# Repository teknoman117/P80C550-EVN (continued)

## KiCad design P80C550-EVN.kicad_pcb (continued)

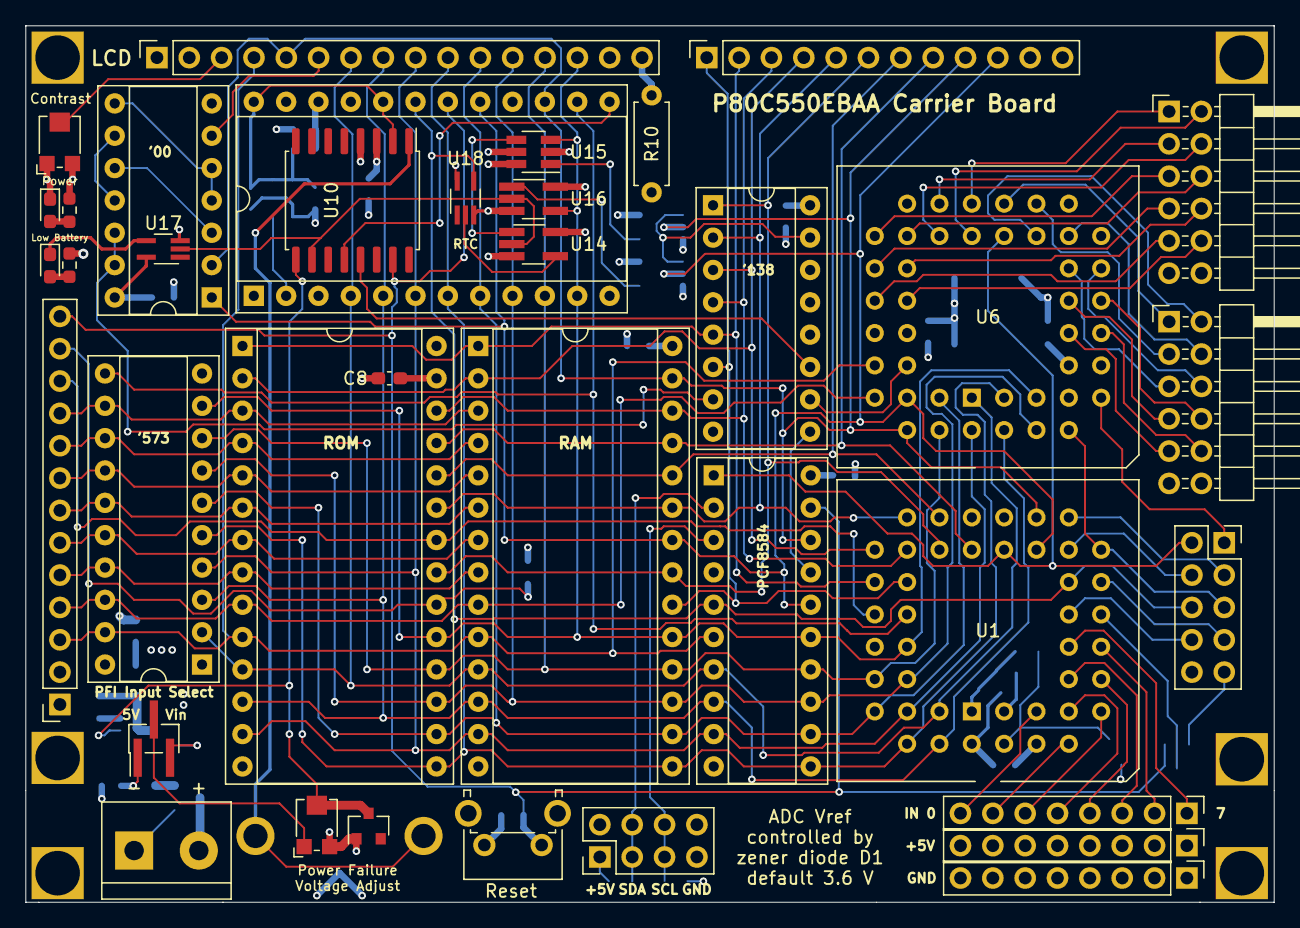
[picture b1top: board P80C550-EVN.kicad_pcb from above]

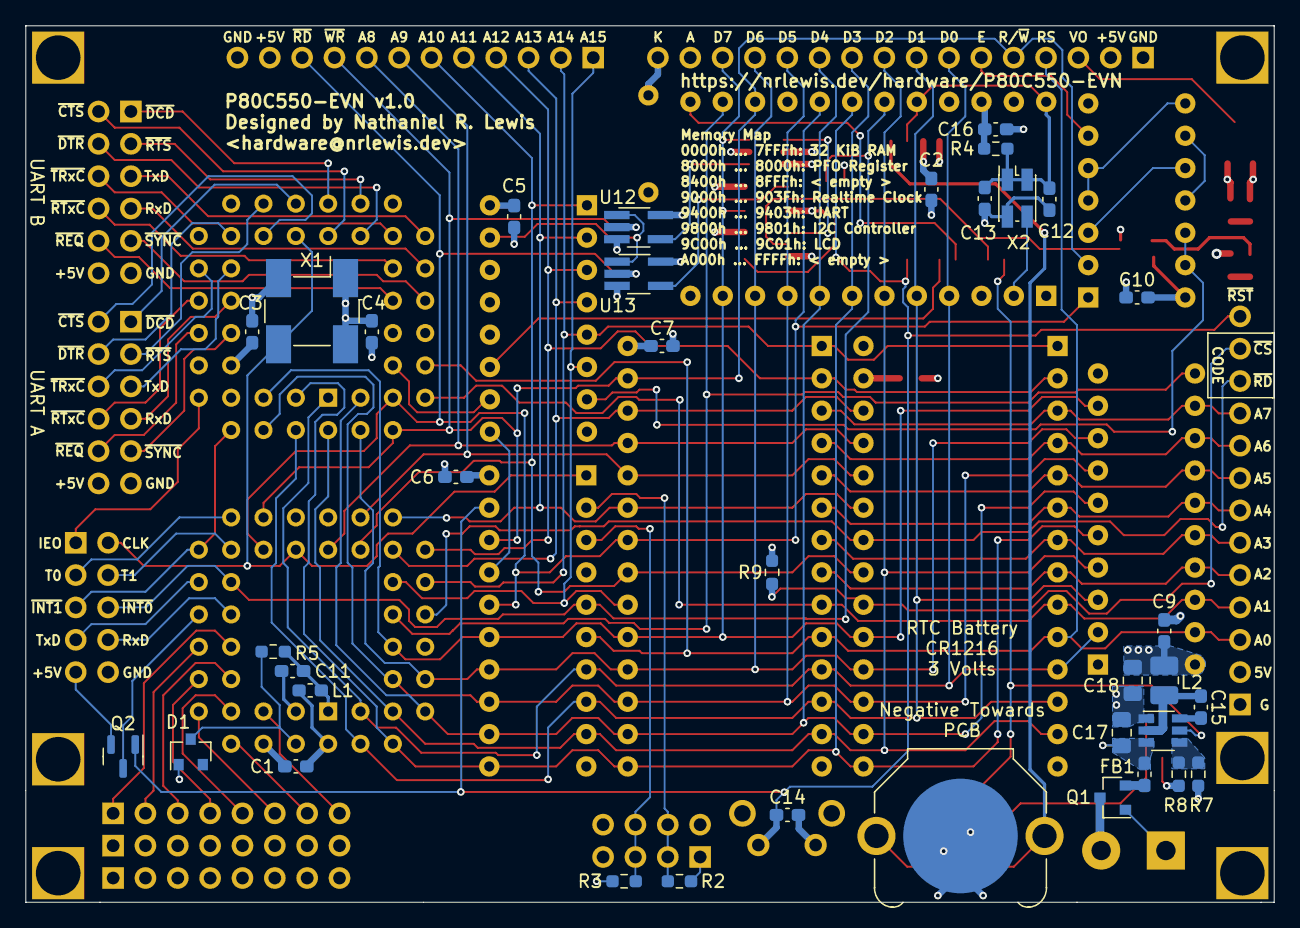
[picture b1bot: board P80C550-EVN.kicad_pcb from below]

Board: 4 copper layers, 98.0 x 68.8 mm, 79 parts (36 on the bottom side), 105 nets.

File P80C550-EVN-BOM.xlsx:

Component | Quantity | Quantity 5x | Part Name | Digikey Part Number | Digikey Website Link | Manufacturer Part Number
BT1 | 1 | 5 | RTC Backup | 36-3001-ND‎ | https://www.digikey.com/product-detail/en/3001/36-3001-ND/227442 | 3001
C16 | 1 | 5 | 5.1nF | 478-06033C512JAT4ACT-ND | https://www.digikey.com/en/products/detail/avx-corporation/0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 | 06033C512JAT4A
C17 | 1 | 5 | 10uF | 587-2985-1-ND | https://www.digikey.com/en/products/detail/taiyo-yuden/TMK21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 | TMK212BBJ106KG-T
C18 | 1 | 5 | 22uF | 587-5464-1-ND | https://www.digikey.com/en/products/detail/taiyo-yuden/LMK21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 | LMK212BBJ226MG-T
C1 C2 C3 C4 C5 C6 C7 C8 C9 C10 C11 C12 C13 C14 C15 | 15 | 75 | 0.1uF | 445-1316-1-ND‎ | https://www.digikey.com/product-detail/en/C1608X7R1E104K080A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 | C1608X7R1E104K080AA
D1 | 1 | 5 | 3.6V (zener) | 1727-5033-1-ND‎ | https://www.digikey.com/product-detail/en/BZX84-C3V6%2c215/1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 | BZX84-C3V6,215
D1 (alt) | 1 | 5 | 3.3V (zener) | 1727-2129-1-ND | https://www.digikey.com/en/products/detail/nexperia-usa-inc/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 | BZX84-C3V3,235
D2 | 1 | 5 | 5.1V (zener) | 1727-2130-1-ND‎ | https://www.digikey.com/product-detail/en/BZX84-C5V1%2c235/1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 | BZX84-C5V1,235
D3 | 1 | 5 | Blue | ‎1830-1068-1-ND‎ | https://www.digikey.com/product-detail/en/IN-S63BT5B/1830-10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 | IN-S63BT5B
D4 | 1 | 5 | Yellow | 1830-1072-1-ND‎ | https://www.digikey.com/product-detail/en/IN-S63BTR/1830-107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 | IN-S63BTR
FB1 | 1 | 5 | 100 @ 100 MHz | 587-1738-1-ND‎ | https://www.digikey.com/product-detail/en/FBMH1608HM101-T/58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 | FBMH1608HM101-T
J1 | 1 | 5 | VIN | 1920-1323-ND | https://www.digikey.com/en/products/detail/altech-corporatio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 | 34.102
J2 | 1 | 5 | Signals | S7108-ND | https://www.digikey.com/en/products/detail/PPPC052LFBN-RC/S7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 | PPPC052LFBN-RC
J3 | 1 | 5 | Address Low | S7046-ND | https://www.digikey.com/en/products/detail/PPPC131LFBN-RC/S7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 | PPPC131LFBN-RC
J4 | 1 | 5 | Address High | S7046-ND | https://www.digikey.com/en/products/detail/PPPC131LFBN-RC/S7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 | PPPC131LFBN-RC
J5 | 1 | 5 | LCD | S7049-ND | https://www.digikey.com/en/products/detail/PPPC161LFBN-RC/S7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 | PPPC161LFBN-RC
J6 J7 | 2 | 10 | UART | S2111EC-06-ND | https://www.digikey.com/en/products/detail/sullins-connector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 | PRPC006DBAN-M71RC
J8 | 1 | 5 | I2C | S2011EC-04-ND | https://www.digikey.com/en/products/detail/sullins-connector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 | PRPC004DAAN-RC
J9 J10 J11 | 3 | 15 | Analog In | S1011EC-08-ND | https://www.digikey.com/en/products/detail/sullins-connector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 | PRPC008SAAN-RC
JP1 | 1 | 5 | PFI Select | 952-3607-ND | https://www.digikey.com/en/products/detail/harwin-inc/M50-36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 | M50-3630342
L1 | 1 | 5 | 39uH | 712-1441-1-ND‎ | https://www.digikey.com/product-detail/en/L-14C39NJV4T/712-1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 | L-14C39NJV4T
L2 | 1 | 5 | 4.7uH | 535-12797-1-ND | https://www.digikey.com/en/products/detail/abracon-llc/AIML-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 | AIML-1008HC-4R7M-T
Q1 | 1 | 5 | Si2393DS | ‎742-SI2393DS-T1-GE3CT-ND‎ | https://www.digikey.com/product-detail/en/SI2393DS-T1-GE3/74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 | SI2393DS-T1-GE3
R1 R2 R3 R4 R5 R6 | 6 | 30 | 2K2 ohms | 118-CR0603-FX-2201ELFCT-ND‎ | https://www.digikey.com/product-detail/en/CR0603-FX-2201ELF/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 | CR0603-FX-2201ELF
R7 | 1 | 5 | 10K ohms | CR0603-FX-1002ELFCT-ND | https://www.digikey.com/en/products/detail/bourns-inc/CR0603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 | CR0603-FX-1002ELF
R8 | 1 | 5 | 52K3 ohms | CR0603-FX-5232ELFCT-ND | https://www.digikey.com/en/products/detail/bourns-inc/CR0603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 | CR0603-FX-5232ELF
R9 | 1 | 5 | 680 ohms | 118-CR0603-JW-681ELFCT-ND‎ | https://www.digikey.com/product-detail/en/CR0603-JW-681ELF/1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 | CR0603-JW-681ELF
R10 | 1 | 5 | 220 ohms
RV1 RV2 | 2 | 10 | 20K | TC33X-1-203ECT-ND | https://www.digikey.com/en/products/detail/TC33X-1-203E/TC33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 | TC33X-1-203E
SW1 | 1 | 5 | Reset | CKN10909-ND | https://www.digikey.com/en/products/detail/c-k/PTS645VM39-2-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 | PTS645VM39-2 LFS
U1 | 1 | 5 | P80C550EBAA
U10 | 1 | 5 | MAX691xWE
U11 | 1 | 5 | AP62150WU-7 | 31-AP62150WU-7CT-ND | https://www.digikey.com/en/products/detail/diodes-incorporat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 | AP62150WU-7
U12 U13 U14 | 3 | 15 | 74VHC1G02 | MC74VHC1G02DTT1GOSCT-ND‎ | https://www.digikey.com/product-detail/en/MC74VHC1G02DTT1G/M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 | MC74VHC1G02DTT1G
U15 | 1 | 5 | 74LVC1G373 | 296-18588-1-ND‎ | https://www.digikey.com/product-detail/en/SN74LVC1G373DBVR/2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 | SN74LVC1G373DBVR
U16 | 1 | 5 | 74VHC1G126 | M74VHC1G126DTT1GOSCT-ND‎ | https://www.digikey.com/product-detail/en/M74VHC1G126DTT1G/M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 | M74VHC1G126DTT1G
U17 | 1 | 5 | 74LVC1G07 | 1727-1181-1-ND‎ | https://www.digikey.com/product-detail/en/74LVC1G07GW-Q100H/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 | 74LVC1G07GW-Q100H
U18 | 1 | 5 | 74LVC1G06 | 1727-6064-1-ND‎ | https://www.digikey.com/product-detail/en/74LVC1G06GW%2c125/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 | 74LVC1G06GW,125
U2 | 1 | 5 | 74AC573 | 296-1379-5-ND | https://www.digikey.com/en/products/detail/CD74AC573E/296-13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 | CD74AC573E
U3 | 1 | 5 | HM62256BLP | AS6C62256-55PCN | https://www.digikey.com/en/products/detail/alliance-memory-i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 | AS6C62256-55PCN
U4 | 1 | 5 | 28C256 | AT28C256-15PU-ND | https://www.digikey.com/en/products/detail/microchip-technol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 | AT28C256-15PU
U5 | 1 | 5 | MC146818
U6 | 1 | 5 | AM85C30 | 269-3927-ND | https://www.digikey.com/en/products/detail/zilog/Z8523016VSG/928917 | Z8523016VSG
U7 | 1 | 5 | 74AHC138 | 296-4225-5-ND | https://www.digikey.com/en/products/detail/CD74AC138E/296-42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 | CD74AC138E
U8 | 1 | 5 | PCF8584
U9 | 1 | 5 | 74AC00 | 296-4214-5-ND | https://www.digikey.com/en/products/detail/CD74AC00E/296-421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 | CD74AC00E
X1 | 1 | 5 | 11.0592 MHz | SER4011CT-ND‎ | https://www.digikey.com/product-detail/en/SG7050CCN+11.05920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 | SG7050CCN 11.059200M-HJGA3
X2 | 1 | 5 | 32.768 KHz | XC1751CT-ND‎ | https://www.digikey.com/product-detail/en/ECS-327KE-TR/XC175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 | ECS-327KE-TR
socket (U1, U6) | 2 | 10 | 44 pin socket | AE10064-ND | https://www.digikey.com/en/products/detail/assmann-wsw-compo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 | A-CCS 044-G-T
socket (U9) | 1 | 5 | 14 pin socket | 2057-ICS-314-T-ND | https://www.digikey.com/en/products/detail/adam-tech/ICS-314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 | ICS-314-T
socket (U7) | 1 | 5 | 16 pin socket | 2057-ICS-316-T-ND | https://www.digikey.com/en/products/detail/adam-tech/ICS-316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 | ICS-316-T
socket (U2, U8) | 2 | 10 | 20 pin socket | 2057-ICS-320-T-ND | https://www.digikey.com/en/products/detail/adam-tech/ICS-320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 | ICS-320-T
socket (U5) | 1 | 5 | 24 pin socket | 2057-ICS-624-T-ND | https://www.digikey.com/en/products/detail/adam-tech/ICS-624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 | ICS-624-T
socket (U3, U4) | 2 | 10 | 28 pin socket | 2057-ICS-628-T-ND | https://www.digikey.com/en/products/detail/adam-tech/ICS-628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 | ICS-628-T
jumper | 1 | 5 | jumper | 2057-HMSC-G-ND | https://www.digikey.com/en/products/detail/adam-tech/HMSC-G/9830451 | HMSC-G
headers (bulk) | 1 | 5 | headers | S1011EC-40-ND | https://www.digikey.com/en/products/detail/sullins-connector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 | PRPC040SAAN-RC

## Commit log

2021-05-02 project state for v1.0
2021-07-22 Add CC-BY-SA 4.0 License
2021-07-22 reorganize gerbers and BOM
2021-07-24 add README.md
2021-07-24 fix some symbol library paths
2021-07-24 add revision history
2021-07-25 add pcb photos
2021-07-25 add photo of expansion connectors in use
2021-07-25 add schematic for v1.0
2023-01-13 update to KiCAD 6.x and fix the non-inverted reset signal by adding a P-Channel MOSFET to invert the inverted reset signal
    Fixes #1 and #2.
